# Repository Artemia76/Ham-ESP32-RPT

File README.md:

<!-- Improved compatibility of back to top link: See: https://github.com/Artemia76/Ham-ESP32-RPT/pull/73 -->

<!--
*** Thanks for checking out the Best-README-Template. If you have a suggestion
*** that would make this better, please fork the repo and create a pull request
*** or simply open an issue with the tag "enhancement".
*** Don't forget to give the project a star!
*** Thanks again! Now go create something AMAZING! :D
-->

<!-- PROJECT SHIELDS -->
<!--
*** I'm using markdown "reference style" links for readability.
*** Reference links are enclosed in brackets [ ] instead of parentheses ( ).
*** See the bottom of this document for the declaration of the reference variables
*** for contributors-url, forks-url, etc. This is an optional, concise syntax you may use.
*** https://www.markdownguide.org/basic-syntax/#reference-style-links
-->
[![Contributors][contributors-shield]][contributors-url]
[![Forks][forks-shield]][forks-url]
[![Stargazers][stars-shield]][stars-url]
[![Issues][issues-shield]][issues-url]
[![GPL v3][license-shield]][license-url]

<!-- PROJECT LOGO -->
<br />
<div align="center">

<h3 align="center">HAM-ESP32-RPT</h3>

  <p align="center">
    An ESP32 Based repeater
    <br />
    <a href="https://github.com/Artemia76/Ham-ESP32-RPT"><strong>Explore the docs »</strong></a>
    <br />
    <br />
    <a href="https://github.com/Artemia76/Ham-ESP32-RPT">View Demo</a>
    &middot;
    <a href="https://github.com/Artemia76/Ham-ESP32-RPT/issues/new?labels=bug&template=bug-report---.md">Report Bug</a>
    &middot;
    <a href="https://github.com/Artemia76/Ham-ESP32-RPT/issues/new?labels=enhancement&template=feature-request---.md">Request Feature</a>
  </p>
</div>

<!-- TABLE OF CONTENTS -->
<details>
  <summary>Table of Contents</summary>
  <ol>
    <li>
      <a href="#about-the-project">About The Project</a>
      <ul>
        <li><a href="#built-with">Built With</a></li>
      </ul>
    </li>
    <li>
      <a href="#getting-started">Getting Started</a>
      <ul>
        <li><a href="#prerequisites">Prerequisites</a></li>
        <li><a href="#installation">Installation</a></li>
      </ul>
    </li>
    <li><a href="#usage">Usage</a></li>
    <li><a href="#roadmap">Roadmap</a></li>
    <li><a href="#contributing">Contributing</a></li>
    <li><a href="#license">License</a></li>
    <li><a href="#contact">Contact</a></li>
    <li><a href="#acknowledgments">Acknowledgments</a></li>
  </ol>
</details>

<!-- ABOUT THE PROJECT -->
## About The Project

[![Product Name Screen Shot][product-screenshot]](https://example.com)

This project aim to purpose universal HAM Radio Analog Repeater based on ESP32 MCU.

It based on :
  * ESP32-S3 DevKit Wroom board
  * PmodI2S2 ADC + DAC I2S moodule
  * INA 219 I2C Voltage measurement chip

In addition (optional) we add :
  * Audio monitoring amplifier
  * Test button
  * Red an Green LED state indication

The Repeater feature are :
  * Stream in the RX audio
  * Stream out the TX audio
  * Play start and end announce
  * Detect 1750 Hz tone to engage
  * Read RSSI value by using voltage reading through _ina219 chip
  * TOT ( time out timer) management
  * Web management through WiFi
  * 

<p align="right">(<a href="#readme-top">back to top</a>)</p>

### Built With

* [![PIO Arduino][PIO.js]][PIO-url]

KiCAD for PCB design

Audacity for wav design

<p align="right">(<a href="#readme-top">back to top</a>)</p>

<!-- GETTING STARTED -->
## Getting Started

This is an example of how you may give instructions on setting up your project locally.
To get a local copy up and running follow these simple example steps.

### Prerequisites

**VS Code**
This project need Microsoft [VS Code IDE](https://code.visualstudio.com)

**PIO Arduino**
Search for `pioarduino` on the [Visual Studio Code Marketplace](https://marketplace.visualstudio.com/search?term=pioarduino&target=VSCode&category=All%20categories&sortBy=Relevance) and follow the documentation [PlatformIO IDE for VSCode](http://docs.platformio.org/page/ide/vscode.html) how to install.

### Installation

_Below is an example of how you can instruct your audience on installing and setting up your app. This template doesn't rely on any external dependencies or services._

1. Clone the repo
   ```sh
   git clone https://github.com/Artemia76/Ham-ESP32-RPT.git
   ```
3. Open folder in VS Code
   
4. Copy and rename the file include/env.hpp.dist to include/env.hpp

5. Enter Wifi Credential has needed in include/env.hpp
   ```
   #define WIFI_SSID "My SSID"
   #define WIFI_PASSWORD "MyVerySecretPassword"
   ```

<p align="right">(<a href="#readme-top">back to top</a>)</p>

<!-- USAGE EXAMPLES -->
## Usage

Use this space to show useful examples of how a project can be used. Additional screenshots, code examples and demos work well in this space. You may also link to more resources.

_For more examples, please refer to the [Documentation](https://example.com)_

<p align="right">(<a href="#readme-top">back to top</a>)</p>

<!-- ROADMAP -->
## Roadmap

- [x] Audio 1750 Hz FFT Detection
- [x] Repeater Sequence
- [X] Web Management
- [X] Permanent Memory
- [ ] PCB Design

See the [open issues](https://github.com/Artemia76/Ham-ESP32-RPT/issues) for a full list of proposed features (and known issues).

<p align="right">(<a href="#readme-top">back to top</a>)</p>

<!-- CONTRIBUTING -->
## Contributing

Contributions are what make the open source community such an amazing place to learn, inspire, and create. Any contributions you make are **greatly appreciated**.

If you have a suggestion that would make this better, please fork the repo and create a pull request. You can also simply open an issue with the tag "enhancement".
Don't forget to give the project a star! Thanks again!

1. Fork the Project
2. Create your Feature Branch (`git checkout -b feature/AmazingFeature`)
3. Commit your Changes (`git commit -m 'Add some AmazingFeature'`)
4. Push to the Branch (`git push origin feature/AmazingFeature`)
5. Open a Pull Request

### Top contributors:

<p align="right">(<a href="#readme-top">back to top</a>)</p>

<!-- LICENSE -->
## License

Distributed under the Unlicense License. See `LICENSE.txt` for more information.

<p align="right">(<a href="#readme-top">back to top</a>)</p>

<!-- CONTACT -->
## Contact

F4IKZ - [@Neophile76](https://twitter.com/artemia76) - neophile76@gmail.com

Project Link: [https://github.com/Artemia76/Ham-ESP32-RPT](https://github.com/Artemia76/Ham-ESP32-RPT)

<p align="right">(<a href="#readme-top">back to top</a>)</p>

<!-- ACKNOWLEDGMENTS -->
## Acknowledgments

Use this space to list resources you find helpful and would like to give credit to. I've included a few of my favorites to kick things off!

* [Choose an Open Source License](https://choosealicense.com)
* [GitHub Emoji Cheat Sheet](https://www.webpagefx.com/tools/emoji-cheat-sheet)
* [Malven's Flexbox Cheatsheet](https://flexbox.malven.co/)
* [Malven's Grid Cheatsheet](https://grid.malven.co/)
* [Img Shields](https://shields.io)
* [GitHub Pages](https://pages.github.com)
* [Font Awesome](https://fontawesome.com)
* [React Icons](https://react-icons.github.io/react-icons/search)

<p align="right">(<a href="#readme-top">back to top</a>)</p>

<!-- MARKDOWN LINKS & IMAGES -->
<!-- https://www.markdownguide.org/basic-syntax/#reference-style-links -->
[contributors-shield]: https://img.shields.io/github/contributors/othneildrew/Best-README-Template.svg?style=for-the-badge
[contributors-url]: https://github.com/Artemia76/Ham-ESP32-RPT/graphs/contributors
[forks-shield]: https://img.shields.io/github/forks/othneildrew/Best-README-Template.svg?style=for-the-badge
[forks-url]: https://github.com/Artemia76/Ham-ESP32-RPT/network/members
[stars-shield]: https://img.shields.io/github/stars/othneildrew/Best-README-Template.svg?style=for-the-badge
[stars-url]: https://github.com/Artemia76/Ham-ESP32-RPT/stargazers
[issues-shield]: https://img.shields.io/github/issues/othneildrew/Best-README-Template.svg?style=for-the-badge
[issues-url]: https://github.com/Artemia76/Ham-ESP32-RPT/issues
[license-shield]: https://img.shields.io/github/license/othneildrew/Best-README-Template.svg?style=for-the-badge
[license-url]: https://github.com/Artemia76/Ham-ESP32-RPT/blob/master/LICENSE.txt
[product-screenshot]: images/screenshot.jpg
[PIO.js]: https://img.shields.io/badge/pioarduino-000000?style=for-the-badge&logo=pioarduino&logoColor=white
[PIO-url]: https://github.com/pioarduino

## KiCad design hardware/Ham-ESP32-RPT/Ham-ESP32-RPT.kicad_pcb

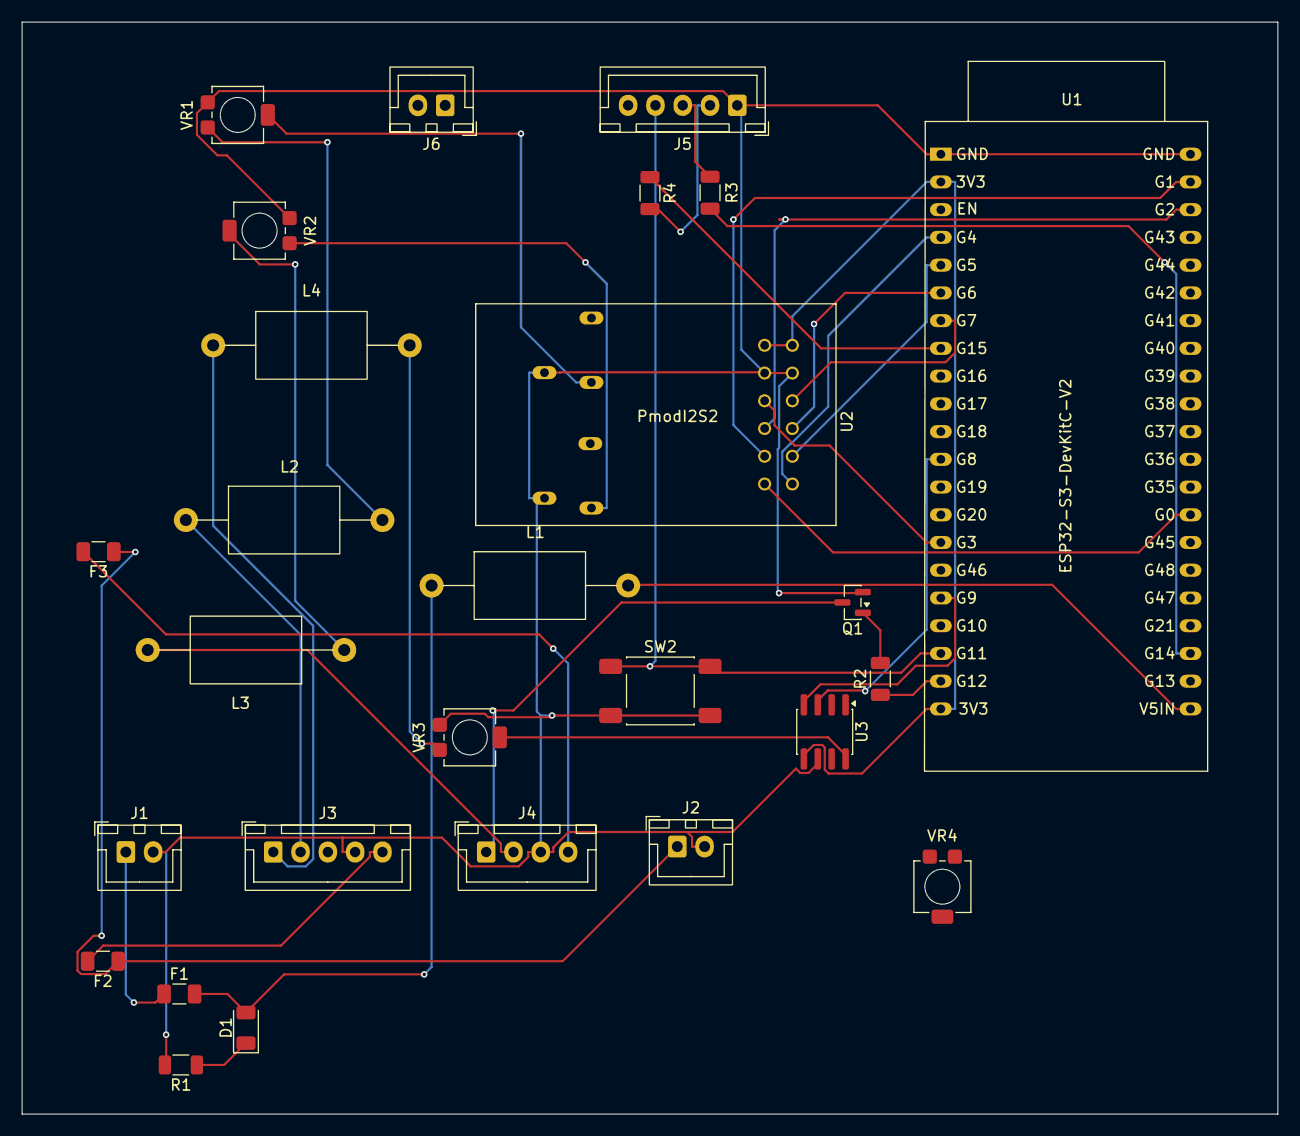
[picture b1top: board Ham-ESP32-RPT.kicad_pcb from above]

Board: 2 copper layers, 115.0 x 100.0 mm, 27 parts (0 on the bottom side), 35 nets.

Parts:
D1: BLUE; LED_1206_3216Metric
F1: 2A; Fuse_1206_3216Metric
F2, F3: 4A; Fuse_1206_3216Metric
J1: 5V SUPPLY; JST_XH_B2B-XH-A_1x02_P2.50mm_Vertical
J2: 12V SUPPLY; JST_XH_B2B-XH-A_1x02_P2.50mm_Vertical
J3: RX RADIO; JST_XH_B5B-XH-A_1x05_P2.50mm_Vertical
J4: TX RADIO; JST_XH_B4B-XH-A_1x04_P2.50mm_Vertical
J5: AUX BTN LED; JST_XH_B5B-XH-A_1x05_P2.50mm_Vertical
J6: SPEAKER; JST_XH_B2B-XH-A_1x02_P2.50mm_Vertical
L1, L2, L3, L4: VK200
Q1: MMBT2222A; SOT-23
R1, R3, R4: 330R; R_1206_3216Metric
R2: 3.3K; R_1206_3216Metric
SW2: TEST; SW_Push_1P1T_NO_E-Switch_TL3301NxxxxxG
U1: ESP32-S3-DevKitC-V2
U2: PmodI2S2
U3: INA219AxD; SOIC-8_3.9x4.9mm_P1.27mm
VR1, VR2, VR3, VR4: 10K; Potentiometer_Bourns_3314R-1_Vertical_Hole

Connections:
+3.3V: U1.2 (3V3), U1.21 (3V3), U2.6 (3V3), U2.12 (3V3), U3.5 (VS)
+5V: L1.2, U1.22 (5V)
GND: J1.2, J2.2, J3.4, J4.3, J5.1, Q1.2 (E), R1.2, SW2.2, U1.1 (GND), U1.42 (GND), U2.5 (GND), U2.11 (GND), U2.15 (A_IN_GND), U2.18 (A_OUT_GND), U3.6 (GND), VR1.1, VR2.3, VR3.1, VR4.1
unnamed: D1.2 (A), F1.2, L1.1
unnamed: D1.1 (K), R1.1
unnamed: F1.1, J1.1
unnamed: F2.1, F3.1, J2.1
unnamed: J3.1, L4.1
unnamed: J3.2, L2.1
unnamed: F2.2, J3.5
unnamed: J4.1, Q1.3 (C)
unnamed: J4.2, L3.2
unnamed: F3.2, J4.4
unnamed: J5.2, R4.2
unnamed: J5.3, R3.2
unnamed: J5.4, SW2.1, U1.19 (G11)
unnamed: L2.2, VR1.3
unnamed: L3.1, VR2.2
unnamed: L4.2, VR3.3
unnamed: Q1.1 (B), R2.2
unnamed: U1.29 (G0), U2.1 (ADOUT_MCLK)
unnamed: U1.41 (G1), U2.2 (ADOUT_LRCK)
unnamed: U1.40 (G2), U2.3 (ADOUT_SCLK)
unnamed: U1.15 (G3), U2.4 (ADOUT_SDIN)
unnamed: U1.4 (G4), U2.7 (ADIN_MCLK)
unnamed: U1.5 (G5), U2.8 (ADIN_LRCK)
unnamed: U1.6 (G6), U2.9 (ADIN_SCLK)
unnamed: U1.7 (G7), U2.10 (ADIN_SDOUT)
unnamed: U1.12 (G8), U3.3 (SDA)
unnamed: U1.17 (G9), U3.4 (SCL)
unnamed: R2.1, U1.20 (G12)
unnamed: R3.1, U1.24 (G14)
unnamed: R4.1, U1.8 (G15)
unnamed: U2.13 (A_IN_L), VR1.2
unnamed: U2.16 (A_OUT_L), VR2.1, VR4.3

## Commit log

2025-01-23 Initial Repo
2025-01-24 annonce
2025-01-25 improve audio
2025-01-25 amélioration du switch voix/relais
2025-01-25 Comment source code
2025-01-26 Add kicad project
2025-01-29 Mise à jour de la documentation
2025-02-02 Add BOM to project
2025-02-02 Using Mutlioutput
2025-02-02 Set mixing mode
2025-02-02 Add CTCSS
2025-02-02 Player Adjustment
2025-02-03 Mise à jour documents
2025-02-03 Change sound announce
2025-02-05 Mise à jour Wifi
2025-02-07 update gitignore
2025-02-07 remove vscode folder
2025-02-07 add web frontend
2025-02-08 Web server
2025-02-09 retrograde auditools
2025-02-09 retrograde audiotools
2025-02-11 WebServer move to core 0 to free core 1
2025-02-14 Disclaimer update
2025-02-24 separate class
2025-03-04 Continue Refactoring
2025-03-05 Refactoring
2025-04-08 Classify Project
2025-04-14 Add documentation
2025-04-14 Audio file sound implementation
2025-04-15 adapt player to project usage
2025-04-27 Mise au point
2025-04-29 doc HAM-ESP32
2025-04-29 remove env.hpp
2025-04-29 add env instruction
2025-04-29 Adjust sound wav
2025-04-29 Add TOT and Led blink to carriage detect
2025-04-29 Correct Merge issue
2025-05-04 Audioin mute when no CD
2025-05-10 Add comment in source files
2025-05-11 CD Correction
2025-06-10 Correct bug for PTT output
2025-06-13 Update Kicad Schematic
2025-06-13 update PCB
2025-06-15 Reduce 1750Hz detection timer
2025-06-15 Add DAC ans ADC documentation
2025-07-15 Relevé d'étalonnage du RSSI
2025-07-20 Change RSSI detection
2025-07-20 I2C adjustment
2025-07-27 Setting Threshold
2025-08-02 Test fonction transfert
2025-08-02 wifi rssi
2025-08-08 Improve HTML dashboard
2025-08-11 Update JS method ,name
2025-09-01 Add Wifi RSSI Measurement
2025-09-02 Fusion avec bnranch main
2025-09-02 log improvement
2025-09-06 Improve Web Server
2025-09-10 Migrate to ESP32 Core v3
2025-09-10 Correct board type in project
2025-09-10 Add readme.md and license txt
2025-09-10 clean comment code
2025-09-13 Add config stored value
2025-09-14 Update Lib audio changes
2025-09-16 Correction
2025-09-16 Add RSSI conversion Class
2025-09-17 Enhance Repeater Sequence
2025-09-17 Check goog sequence transition for ending repeating
2025-09-21 Settings
2025-09-26 Maj jauge RSSI
2025-09-28 Improve 1750 detection & html squelch
2025-10-02 Modif jauge
2025-10-03 Correction erreur dans le head
2025-10-12 test
2025-10-12 Add 1750 Mag FFT Conf
2025-10-13 Improve CD management
2025-10-19 Correct Input event
2025-10-20 Enhance Player audio volume management
2025-11-04 Add ESP32-S3 pinout documentation
2025-11-24 Add TOT to WEB Dashboard
2025-11-24 Add code comments
2025-12-01 PCB kicad update
2025-12-02 Add TOT Record
2025-12-27 test wifi events
2025-12-27 Add pinout documentation
2025-12-29 Add Wifi reconnect and Audio Volume Adjustment
2026-01-04 Comissionning
2026-02-02 Add Vk200 footprint
2026-02-17 Add PmodI2S2 footprint
2026-02-28 Improve Timer for millis() overflow
2026-02-28 Update Audio lib and start timer bug solve
2026-03-01 Supression pistes
2026-03-01 PCB Update
2026-03-02 CTimer documentation update
2026-03-12 Add Button to test and restart
2026-03-12 Repair Service mode bug
2026-03-30 Correct button position
2026-03-30 Thread safety fix
2026-04-17 New dev for account implementation
2026-04-28 Add Roger Beep Filter
2026-06-12 update PCB diagram
